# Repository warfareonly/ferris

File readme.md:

Meet Ferris, a minimalistic keyboard
====================================

Named after the Rustlang mascott, ferris is a 34 keys split keyboard that tries to be about as cute as its namesake.

Ferris is minimalistic: it aims to be a functional, ergonomic keyboard that is pleasing to use as a daily driver. It only supports choc keyswitches, although it would be easy to make a MX version if there was interest.

It is fully Open-Source: the kicad files are released under [the solderpad license, version 2.1](LICENSE). The firmware, contributed to [the QMK project](https://github.com/qmk/qmk_firmware/) is released under the GPL.

Design philosophy
-----------------

The Ferris was designed around this set of goals:
* Comfort
* Aesthetics
* Portability
* Ease of assembly
* Low-Cost
* Low-Profile
* 34 keys
* Hackable
* USB-C
* No compromise

and this set of non-goals:
* Reversible PCB used for both hands
* Pro-micro/Elite C/Proton C support
* Hot-Swap support
* Multi-switches support
* Support for any feature (RGB, OLED, encoders, ...) that is not of interest to the user

You may read more about how each feature (and mostly lack thereof) contributes to these goals [in this write up](docs/design_philosophy.md) once described as "overly long and almost pretentious" :)

Technical details
-----------------

### Base variant, rev 0.1

This describes the first ever iteration of the Ferris keyboard: a plain pcb with support for choc switches, and the same layout as the Kyria (but limited to 34 keys).

* USB C
* 34 keys (3x5 + 2 thumb keys per hand)
* Split
* Atmega32u4 microcontroller on the left hand side
* MCP23017 on the right hand side
* A 4 poles jack cable carries data between halves using the i2c protocol
* The diodes live under the switches where they are snuggly hidden from sight
* No holes through the PCB. The intent is to use it case-less.
* Switches are spaced by 19mm from each other in each direction (almost exactly what's known as MX spacing [19.05x19.05]). This allows for a wider variety of compatible keycaps for the price of gaps for certain keycaps that respect the Kailh choc specification
* Columnar stagger identical to the one on the Kyria

### Ferris low variant, rev 0.1

* Same as the base variant with major change that the footprints are for Kailh PG1232 instead of choc for an even lower profile
* Copper pad adapted to ducking Ferris for theme
* Silkscreen changed to display schematics from the PG1232 switch
* Recommended PCB solder mask color is blue instead of white so the silkscreen gives vibes of a blueprint
* Name of the board updated to "Ferris low" instead of "Ferris"

### Upcoming changes

In rev 0.2, I would like to implement the following changes:

* Microcontroller: [Arm STM32F030F4P6TR](https://lcsc.com/product-detail/Others_STMicroelectronics_STM32F030F4P6TR_STMicroelectronics-STM32F030F4P6TR_C89040.html) instead of [Atmega32u4](https://lcsc.com/product-detail/ATMEL-AVR_ATMEL_ATMEGA32U4-AU_ATMEGA32U4-AU_C44854.html)
  * Cheaper: 0.83$ instead of $3.63, less unused pins, easier to solder, more flash, more ram, better rust support for possible pure rust firmware
* IO Expander: [PCA9539PW ](https://lcsc.com/product-detail/I-O-Expansion_NXP_PCA9539PW_PCA9539PW_C129516.html) instead of [MCP23017](https://lcsc.com/product-detail/Interface-ICs_MICROCHIP_MCP23017-E-SO_MCP23017-E-SO_C47023.html)
  * Cheaper 0.76$ instead of 1.56$
* Spacing: 0.18x0.19 instead of 0.19x0.19
  * Avoids gaps with keycaps that conform with the Kailh specifications
  * More ergonomic as fingers don't have to move as far up and down
  * Con: Looses compatibility to some keycaps
* Ferris MX:
  * I would like to also do a run with MX only footprints for anyone interested
* Ferris tent:
  * I would like to add four mounting holes on each hand to support the tenting puck that Thomas Baart at splitkb.com is currently designing

How to I print one?
-------------------

For a given version, you will find a release in this repository containing a zip file with the gerber files. This should be ready to send to a PCB manufacturer for assembly.
The repository also contains a bill of materials (bom.csv) with a list of the components you need and their reference number on LCSC.com. You may use another vendor for the components, as long as you make sure to get components that are equivalent.

How do I assemble one?
----------------------

Here is where the components go on the pcb:

Most of these components are smd mounted. They can be soldered in with hot air and solder paste or with a soldering iron, solder wire and flux.
I have found it easier to control how much solder I use with a soldering iron.

Here are some key pieces of advice I can give from my experience assembling 3 of them so far:
* Be mindful of the orientation for the components that are polarized:
  * Diodes: cathode bar on the right side for both pcbs
  * Crystal: text readable looking at it from the controller
  * Controller: pin 1 dot indicator in the top right
  * IO expander: pin 1 dot indicator in the top left
* Use a wedge tip or other tip with a large enough surface. Pointy is harder.
* Don't use too much solder or you will have to wick it away and start again.
  * This especially applies to the USB C area and the microcontroller.
* Don't be shy on the flux: it really helps the solder flow where it should and keep away from surfaces it shouldn't go to.
* Don't use too much heat to avoid damaging the components. I've had good results with 350C for unleaded rosin core solder wire.
* Don't touch any component for too long with the iron to avoid heat damage. If you're not getting it right in a few seconds, let it cool down add more flux and try again. 
* Be sure to test every diode is properly soldered before soldering on the switches as the diodes are located under the switches and won't be accessible later on.
* I have found it easier to solder the crystal with hot air as it is hard to reach the solder from under it with an iron. Your mileage may vary

I took many pictures while building a board. If you want to build a Ferris while following along,
Part 1:
[build log, part 1](https://imgur.com/gallery/jYbxkxE)
Part 2:
[build log, part 2](https://imgur.com/gallery/gs19F6E)

Where is the firmware?
----------------------

For now, the Ferris keyboard is powered by QMK. Firmware for it is available [in this PR](https://github.com/qmk/qmk_firmware/pull/9634) and should make it upstream once the review process has taken its course.

The default keymap is very minimalistic. I will come up with something fancier in due time.

Status:
-------
v 0.1 is confirmed to work: I have printed 5 on jlcpcb.com and assembled 3. I have flashed the firmware on all of these and made sure that all keys are recognized as intended. I am also typing these words on a Ferris.

Here is a short demo of a working Ferris:
[typing test](https://i.imgur.com/E8Wipxz.mp4)

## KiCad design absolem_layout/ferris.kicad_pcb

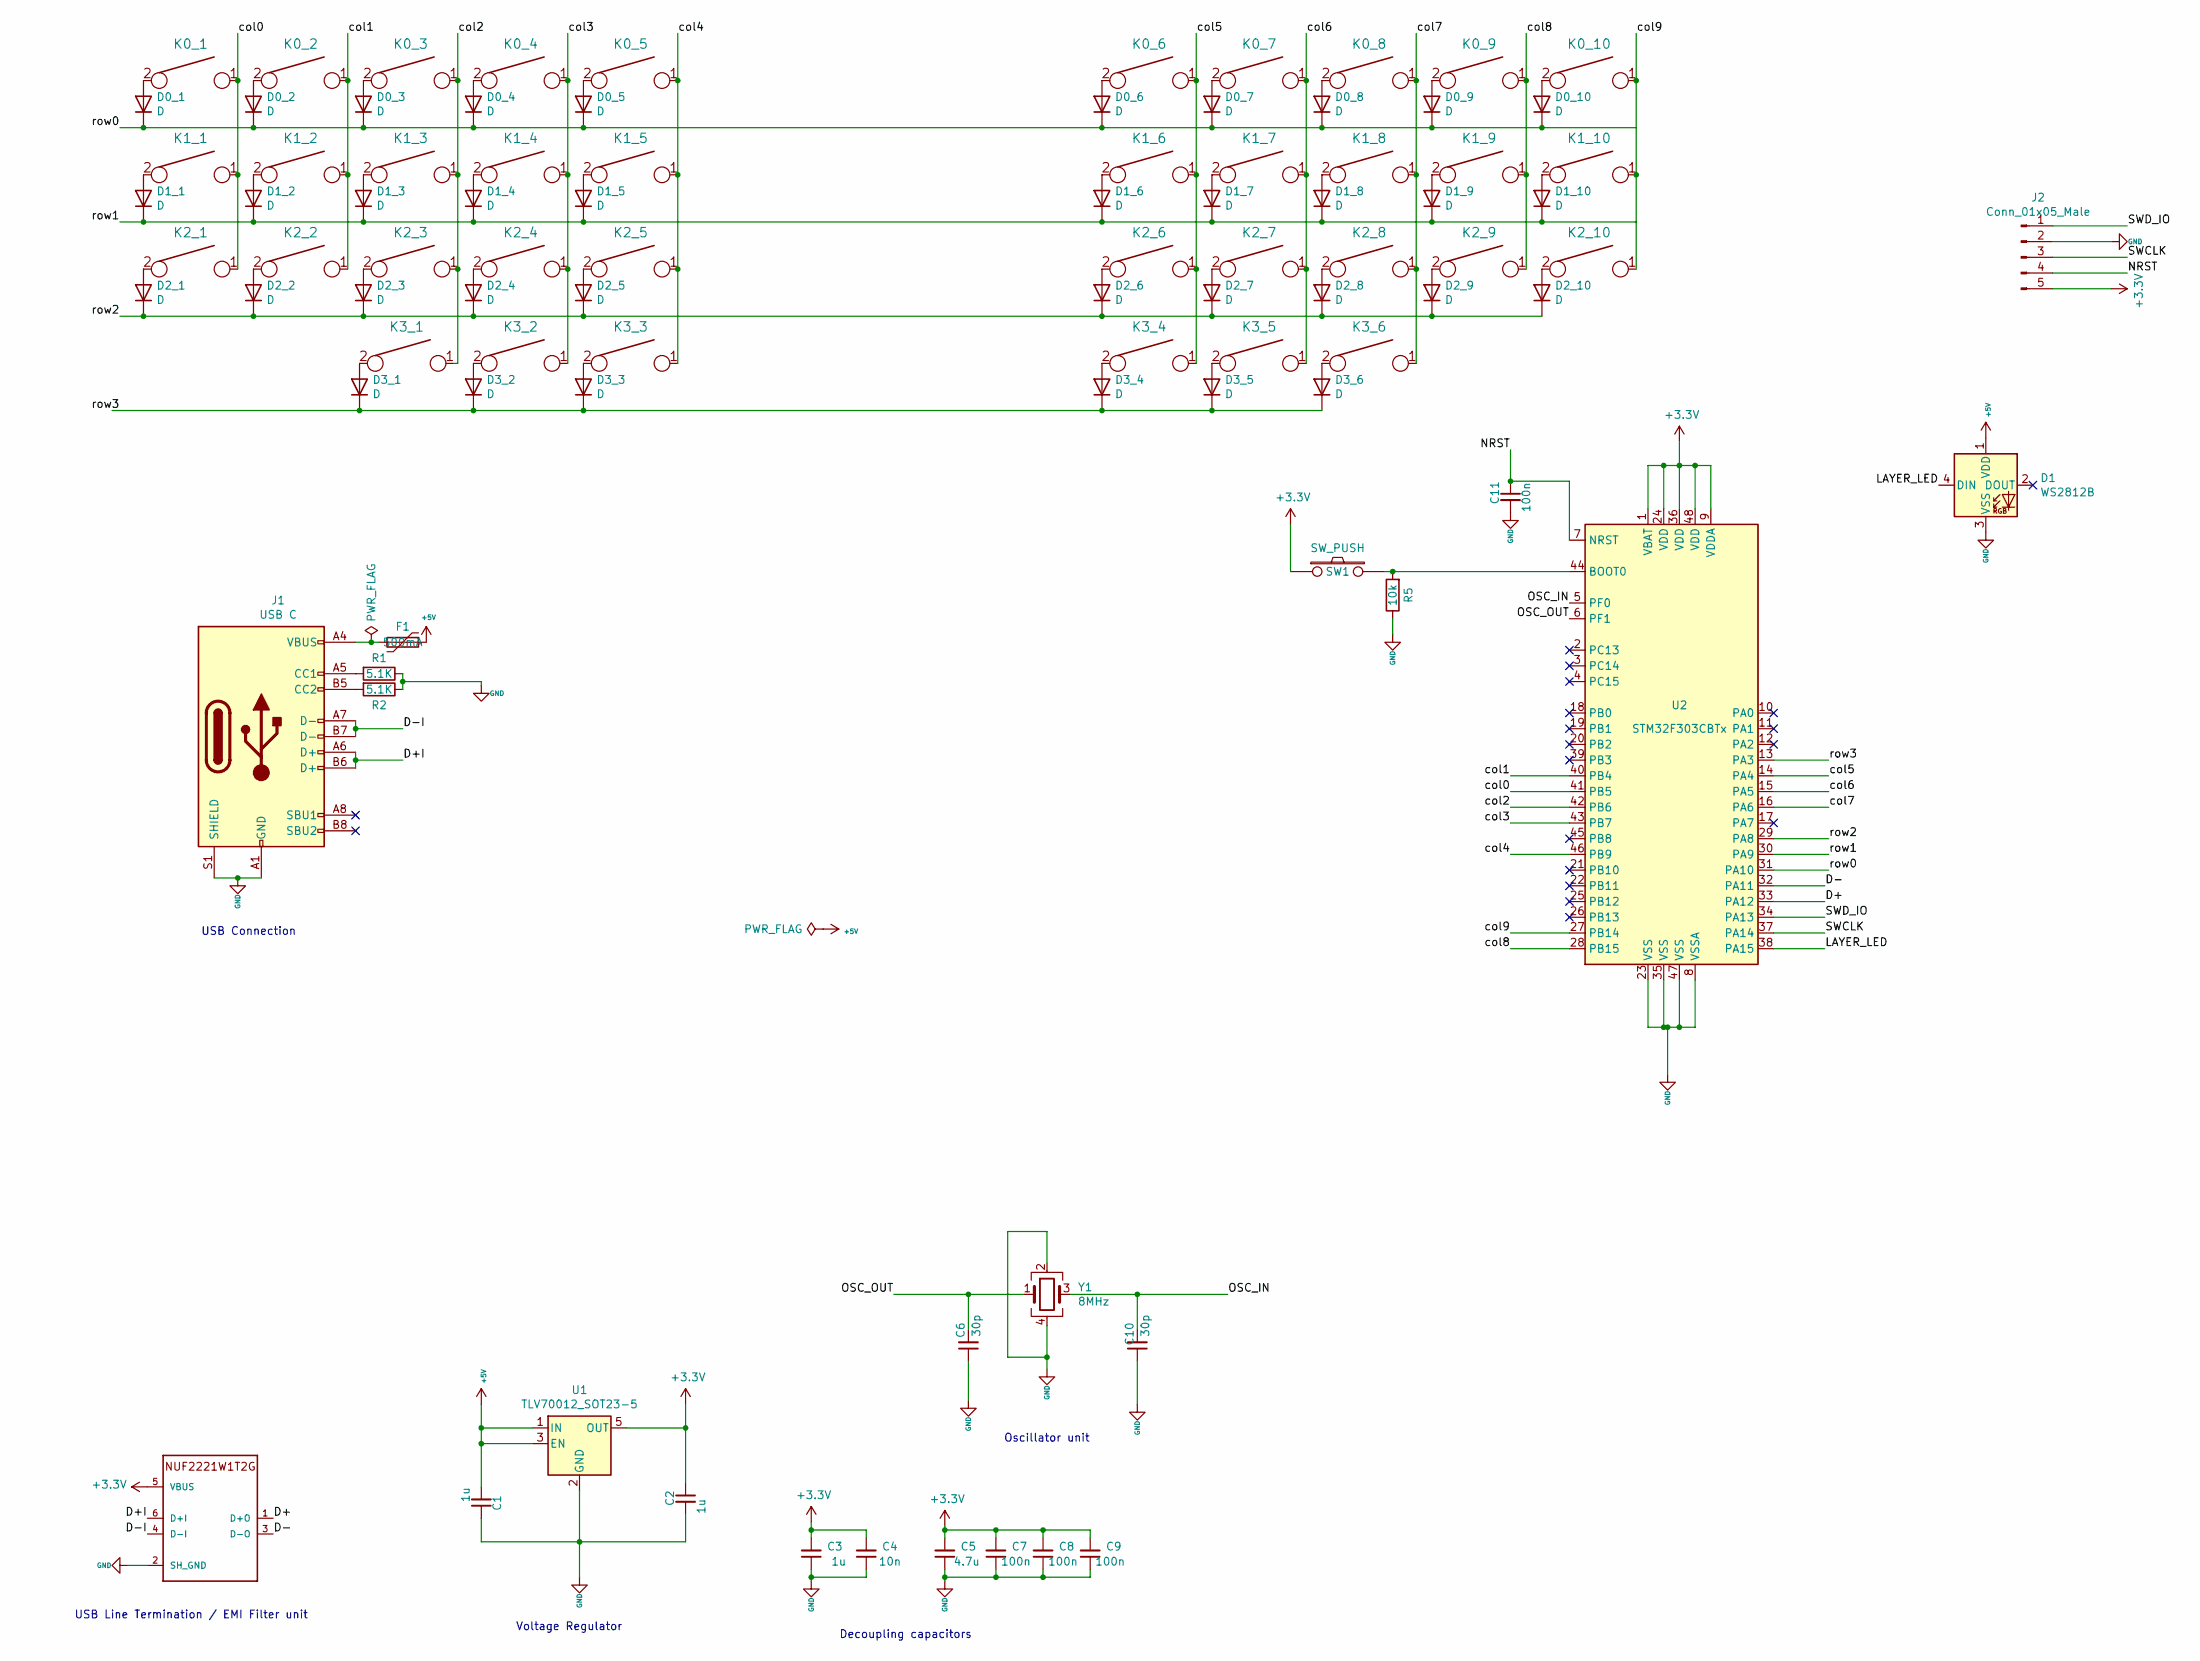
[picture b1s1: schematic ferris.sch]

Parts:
C1, C2: 1u; C_0805_2012Metric_Pad1.15x1.40mm_HandSolder; LCSC Part # C49678
C3: 1u; C_0805_2012Metric_Pad1.15x1.40mm_HandSolder
C4: 10n; C_0805_2012Metric_Pad1.15x1.40mm_HandSolder
C5: 4.7u; C_0805_2012Metric_Pad1.15x1.40mm_HandSolder
C6, C10: 30p; C_0805_2012Metric_Pad1.15x1.40mm_HandSolder
C7, C8, C9: 100n; C_0805_2012Metric_Pad1.15x1.40mm_HandSolder
C11: 100n; C_0805_2012Metric_Pad1.15x1.40mm_HandSolder; LCSC Part # C49678
D0_1: D; D_SOD-123; LCSC Part # C81598
D0_2, D0_3, D0_4, D0_5, D0_6, D0_7, D0_8, D0_9, D0_10, D1_1, D1_2, D1_3, D1_4, D1_5, D1_6, D1_7, D1_8, D1_9, D1_10, D2_1, D2_2, D2_3, D2_4, D2_5, D2_6, D2_7, D2_8, D2_9, D2_10, D3_1, D3_2, D3_3, D3_4, D3_5, D3_6: D; D_SOD-123
D1: WS2812B; LED_WS2812B_PLCC4_5.0x5.0mm_P3.2mm
F1: 500mA; Fuse_1206_3216Metric; LCSC Part # C151162
IC1: NUF2221W1T2G; SOT-363
J1: USB C; USB_C_Receptacle_HRO_TYPE-C-31-M-12; LCSC Part # C165948
J2: Conn_01x05_Male; PinHeader_1x05_P2.54mm_Vertical
K0_1: KEYSW; MXOnly-1U-NoLED; LCSC Part # C489144
K0_2, K0_3, K0_4, K0_5, K0_6, K0_7, K0_8, K0_9, K0_10, K1_1, K1_2, K1_3, K1_4, K1_5, K1_6, K1_7, K1_8, K1_9, K1_10, K2_1, K2_2, K2_3, K2_4, K2_5, K2_6, K2_7, K2_8, K2_9, K2_10, K3_1, K3_2, K3_3, K3_4, K3_5, K3_6: KEYSW; MXOnly-1U-NoLED
R1: 5.1K; R_0805_2012Metric_Pad1.15x1.40mm_HandSolder; LCSC Part # C27834
R2: 5.1K; R_0805_2012Metric_Pad1.15x1.40mm_HandSolder
R5: 10k; R_0805_2012Metric_Pad1.15x1.40mm_HandSolder; LCSC Part # C17414
SW1: SW_PUSH; SW_SPST_B3U-1000P; LCSC Part # C231329
U1: TLV70012_SOT23-5; SOT-23-5
U2: STM32F303CBTx; LQFP-48_7x7mm_P0.5mm
Y1: 8MHz; Crystal_SMD_5032-4Pin_5.0x3.2mm

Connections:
+3V3: C2.1, C3.2, C4.2, C5.2, C7.2, C8.2, C9.2, IC1.5 (VBUS), J2.5, SW1.1, U1.5 (OUT), U2.1 (VBAT), U2.9 (VDDA), U2.24 (VDD), U2.36 (VDD), U2.48 (VDD)
+5V: C1.2, D1.1 (VDD), F1.1, U1.1 (IN), U1.3 (EN)
/D+: IC1.1 (D+O), U2.33 (PA12)
/D+I: IC1.6 (D+I), J1.A6 (D+), J1.B6 (D+)
/D-: IC1.3 (D-O), U2.32 (PA11)
/D-I: IC1.4 (D-I), J1.A7 (D-), J1.B7 (D-)
/LAYER_LED: D1.4 (DIN), U2.38 (PA15)
/NRST: C11.1, J2.4, U2.7 (NRST)
/OSC_IN: C10.2, U2.5 (PF0), Y1.3
/OSC_OUT: C6.2, U2.6 (PF1), Y1.1
/SWCLK: J2.3, U2.37 (PA14)
/SWD_IO: J2.1, U2.34 (PA13)
/col0: K0_1.1, K1_1.1, K2_1.1, U2.41 (PB5)
/col1: K0_2.1, K1_2.1, K2_2.1, U2.40 (PB4)
/col2: K0_3.1, K1_3.1, K2_3.1, K3_1.1, U2.42 (PB6)
/col3: K0_4.1, K1_4.1, K2_4.1, K3_2.1, U2.43 (PB7)
/col4: K0_5.1, K1_5.1, K2_5.1, K3_3.1, U2.46 (PB9)
/col5: K0_6.1, K1_6.1, K2_6.1, K3_4.1, U2.14 (PA4)
/col6: K0_7.1, K1_7.1, K2_7.1, K3_5.1, U2.15 (PA5)
/col7: K0_8.1, K1_8.1, K2_8.1, K3_6.1, U2.16 (PA6)
/col8: K0_9.1, K1_9.1, K2_9.1, U2.28 (PB15)
/col9: K0_10.1, K1_10.1, K2_10.1, U2.27 (PB14)
/row0: D0_1.1 (K), D0_2.1 (K), D0_3.1 (K), D0_4.1 (K), D0_5.1 (K), D0_6.1 (K), D0_7.1 (K), D0_8.1 (K), D0_9.1 (K), D0_10.1 (K), U2.31 (PA10)
/row1: D1_1.1 (K), D1_2.1 (K), D1_3.1 (K), D1_4.1 (K), D1_5.1 (K), D1_6.1 (K), D1_7.1 (K), D1_8.1 (K), D1_9.1 (K), D1_10.1 (K), U2.30 (PA9)
/row2: D2_1.1 (K), D2_2.1 (K), D2_3.1 (K), D2_4.1 (K), D2_5.1 (K), D2_6.1 (K), D2_7.1 (K), D2_8.1 (K), D2_9.1 (K), D2_10.1 (K), U2.29 (PA8)
/row3: D3_1.1 (K), D3_2.1 (K), D3_3.1 (K), D3_4.1 (K), D3_5.1 (K), D3_6.1 (K), U2.13 (PA3)
GND: C1.1, C2.2, C3.1, C4.1, C5.1, C6.1, C7.1, C8.1, C9.1, C10.1, C11.2, D1.3 (VSS), IC1.2 (SH_GND), J1.A1 (GND), J1.A12 (GND), J1.B1 (GND), J1.B12 (GND), J1.S1 (SHIELD), J2.2, R1.1, R2.1, R5.1, U1.2 (GND), U2.8 (VSSA), U2.23 (VSS), U2.35 (VSS), U2.47 (VSS), Y1.2, Y1.4
unnamed: D0_1.2 (A), K0_1.2
unnamed: D0_2.2 (A), K0_2.2
unnamed: D0_3.2 (A), K0_3.2
unnamed: D0_4.2 (A), K0_4.2
unnamed: D0_5.2 (A), K0_5.2
unnamed: D0_6.2 (A), K0_6.2
unnamed: D0_7.2 (A), K0_7.2
unnamed: D0_8.2 (A), K0_8.2
unnamed: D0_9.2 (A), K0_9.2
unnamed: D0_10.2 (A), K0_10.2
unnamed: D1_1.2 (A), K1_1.2
unnamed: D1_2.2 (A), K1_2.2
unnamed: D1_3.2 (A), K1_3.2
unnamed: D1_4.2 (A), K1_4.2
unnamed: D1_5.2 (A), K1_5.2
unnamed: D1_6.2 (A), K1_6.2
unnamed: D1_7.2 (A), K1_7.2
unnamed: D1_8.2 (A), K1_8.2
unnamed: D1_9.2 (A), K1_9.2
unnamed: D1_10.2 (A), K1_10.2
unnamed: D2_1.2 (A), K2_1.2
unnamed: D2_2.2 (A), K2_2.2
unnamed: D2_3.2 (A), K2_3.2
unnamed: D2_4.2 (A), K2_4.2
unnamed: D2_5.2 (A), K2_5.2
unnamed: D2_6.2 (A), K2_6.2
unnamed: D2_7.2 (A), K2_7.2
unnamed: D2_8.2 (A), K2_8.2
unnamed: D2_9.2 (A), K2_9.2
unnamed: D2_10.2 (A), K2_10.2
unnamed: D3_1.2 (A), K3_1.2
unnamed: D3_2.2 (A), K3_2.2
unnamed: D3_3.2 (A), K3_3.2
unnamed: D3_4.2 (A), K3_4.2
unnamed: D3_5.2 (A), K3_5.2
unnamed: D3_6.2 (A), K3_6.2
unnamed: F1.2, J1.A4 (VBUS), J1.A9 (VBUS), J1.B4 (VBUS), J1.B9 (VBUS)
unnamed: J1.A5 (CC1), R1.2
unnamed: J1.B5 (CC2), R2.2
unnamed: R5.2, SW1.2, U2.44 (BOOT0)

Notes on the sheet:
Voltage Regulator
USB Line Termination / EMI Filter unit
Oscillator unit
Decoupling capacitors
USB Connection

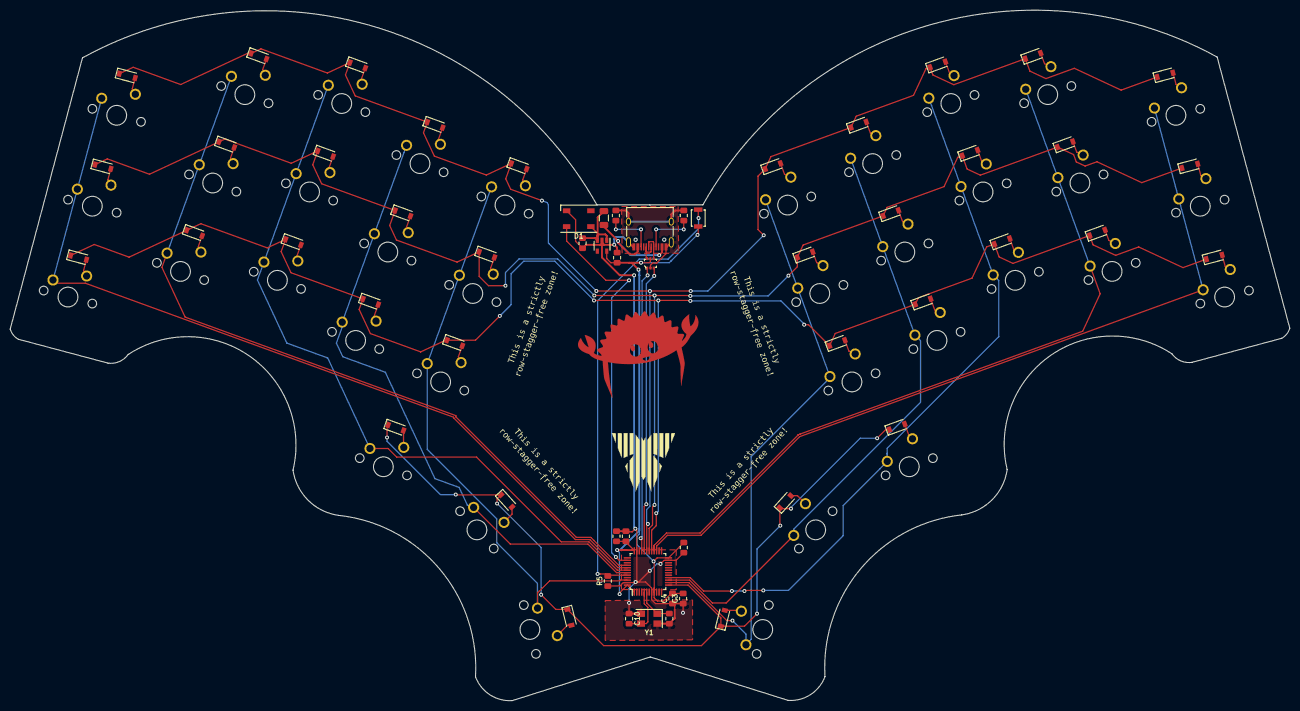
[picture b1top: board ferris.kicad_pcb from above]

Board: 2 copper layers, 258.4 x 139.4 mm, 93 parts (0 on the bottom side), 64 nets.

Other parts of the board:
GFRONT: LOGO; front

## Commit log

2020-07-14 Design the "Ferris low" variant
    * Same as the base variant with major change that the footprints are
    for Kailh PG1232 instead of choc for an even lower profile
    * Copper pad adapted to ducking Ferris for theme
    * Silkscreen changed to display schematics from the PG1232 switch
    * Recommended PCB solder mask color is blue instead of white so the
    silkscreen gives vibes of a blueprint
2020-07-15 Update silkscreen text to credit bomtarnes and for uppercasing Low
2020-07-15 Position credits a bit better
2020-07-30 Added LED on LHS
2020-07-31 Moved I2C resistors to RHS, moved LED
2020-07-31 Replaced MCP23017 with PCA9539PW
2020-07-31 Repositioned the components near the inner edges
2020-07-31 Fixed a minor DRC error
2020-08-01 Cleaned up some tracks. Final stuff editing now
2020-08-04 Rotated pinky col
2020-08-04 some update for the project file
2020-08-04 Traces
2020-08-05 Added a version with the Absolem layout
2020-08-05 Fixed some staggering
2020-08-05 Fixed some minor routing and silksscreen
2020-08-06 Computer change
2020-08-06 Devid commit
2020-08-06 Oscillator added to the schematic.
2020-08-06 Labelling
2020-08-06 Deivid changes.
2020-08-06 More labelling
2020-08-06 More connections, removed line termination resistors (now we use an IC for it!)
2020-08-06 Connected up most of the power. PCB incomplete still
2020-08-07 Updated the routing and positons
2020-08-08 Prefinal version
2020-08-08 Loose trace fixed.
2020-08-08 Final version
